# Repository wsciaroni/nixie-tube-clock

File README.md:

# nixie-tube-clock
Work in progress for designing and building a custom Nixie Tube Clock

## Starting Point

This project is incomplete.

I have started from the really helpful blog here: https://crystal.uta.edu/~burns/project_nixieclock.html

## Overview

I remember my first exposure to Nixie Tubes vividly. It was an old coin counting machine we were using for a change colection fund raiser. I was fascinated by the Nixie Tubes and have never forgotten them.

After observing many other Nixie Clock builds, I decided there wasn't one that met all of my needs.

The closest that I found was here: https://crystal.uta.edu/~burns/project_nixieclock.html. However, I would like a more accurate time. So, I plan to start with this project and modify it.  My goal is to

- Remove the LEDs (I don't really want a backlight)
- Change the embedded system to an ESP8266 / NodeMCU with WiFi to maintain time with the network
- Make sure the programming port is accessible so that I can reprogram or update the firmwware as needed

My Requirements for the clock are as follows

1. The clock needs to use Nixie Tubes
2. The Clock would sync with WiFi to keep a very accurate time
3. The high voltage supply's circuitry will be it's own board for modularity
4. It will be a 6 digit 24-hour clock (H1 H0 : M1 M0 : S1 S0)
5. The clock should be powered via 120V AC

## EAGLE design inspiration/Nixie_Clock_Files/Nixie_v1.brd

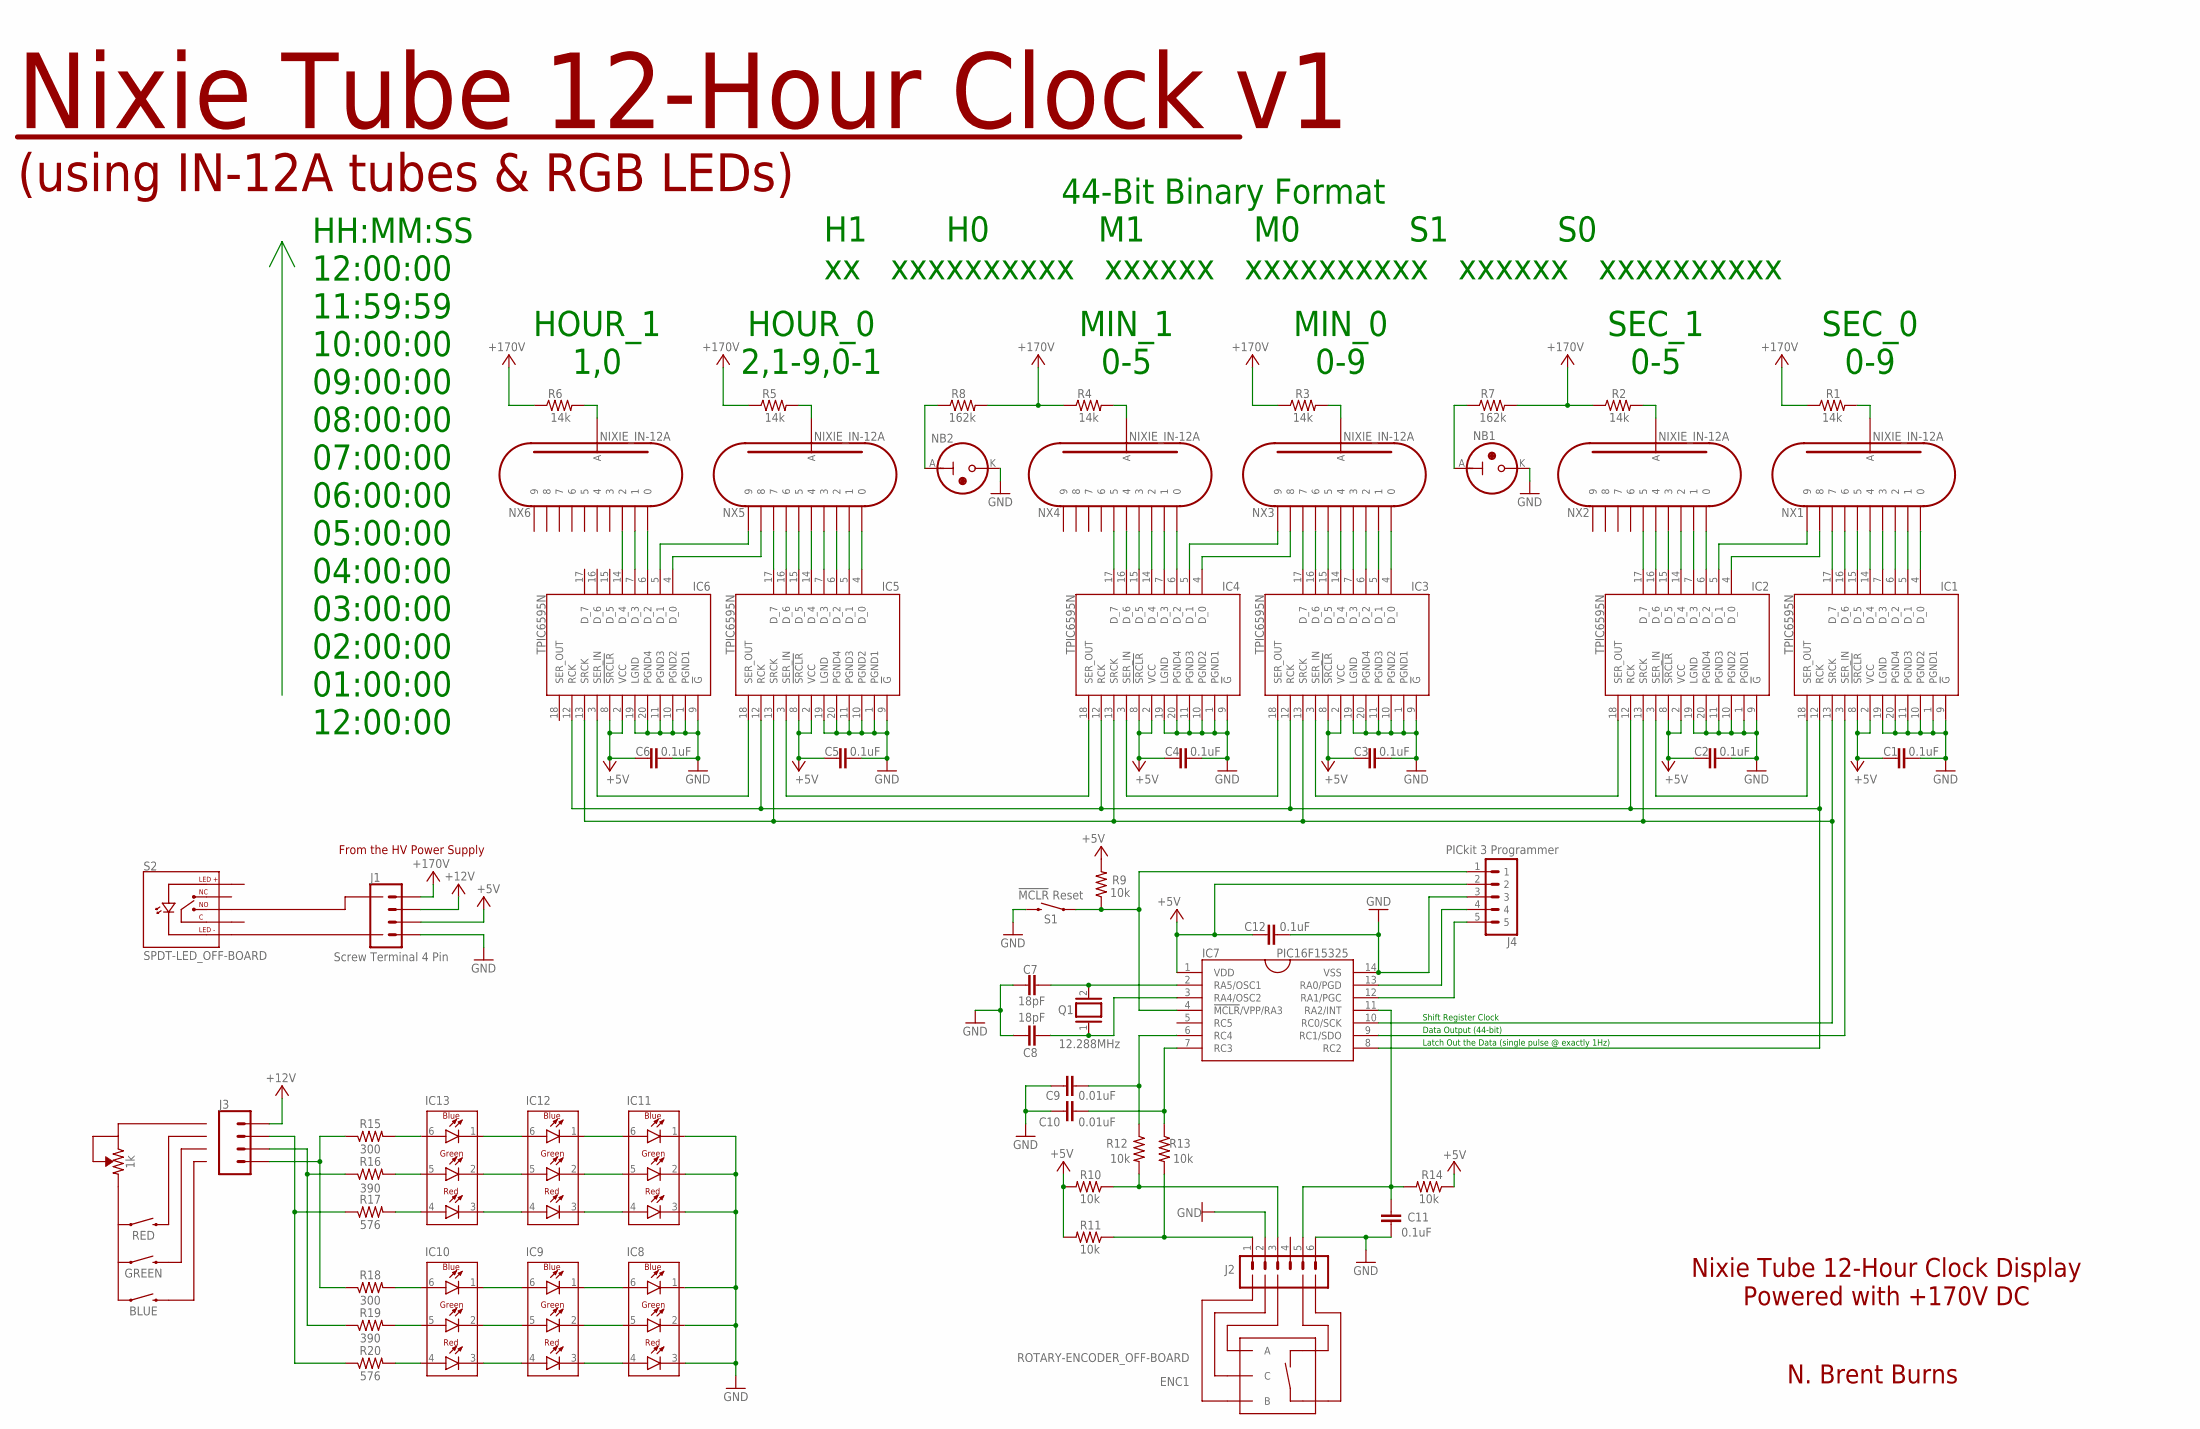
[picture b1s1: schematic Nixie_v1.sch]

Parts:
C1, C2, C3, C4, C5, C6, C11, C12: 0.1uF; C2.5-2
C7, C8: 18pF; C2.5-2
C9, C10: 0.01uF; C2.5-2
IC1, IC2, IC3, IC4, IC5, IC6: TPIC6595N; DIP20
IC7: PIC16F15325; DIP14
IC8, IC9, IC10, IC11, IC12, IC13: LED-RGB_CLY6D-FKC-CK1N1D1BB7D3D3; PLCC6-LED-RGB
J1: Screw Terminal 4 Pin; SCREW_TERM_5MM_1X4
J2: CONNECTOR_6PINSCREW_TERMINAL_5MM_PITCH; SCREW_TERM_5MM_1X6
J3: RGB Switches and 5k POT Connections; SCREW_TERM_5MM_1X4
J4: PICkit 3 Programmer; HEADER_2.54MM_1X5
NB1, NB2: IN-3
NX1, NX2, NX3, NX4, NX5, NX6: NIXIE_IN-12A; IN-12_NO_HOLE
Q1: 12.288MHz; QS
R1, R2, R3, R4, R5, R6: 14k; 0411/12
R7, R8: 162k; 0411/12
R9, R10, R11, R12, R13, R14: 10k; 0207/7
R15, R18: 300; 0207/7
R16, R19: 390; 0207/7
R17, R20: 576; 0207/7
S1: !MCLR! Reset; TACTILE_SWITCH_PTH_6.0MM
SYM101: SYMBOL_HIGH_VOLTAGE

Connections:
+5V: C1.2, C2.2, C3.2, C4.2, C5.2, C6.2, C12.1, IC1.2 (VCC), IC1.8 (!SRCLR), IC2.2 (VCC), IC2.8 (!SRCLR), IC3.2 (VCC), IC3.8 (!SRCLR), IC4.2 (VCC), IC4.8 (!SRCLR), IC5.2 (VCC), IC5.8 (!SRCLR), IC6.2 (VCC), IC6.8 (!SRCLR), IC7.1 (VDD), J1.2, J4.2, R9.2, R10.2, R11.2, R14.1
+12V: J1.3, J3.4
+170V: J1.4, R1.1, R2.1, R3.1, R4.1, R5.1, R6.1, R7.2, R8.2
GND: C1.1, C2.1, C3.1, C4.1, C5.1, C6.1, C7.2, C8.2, C9.2, C10.2, C11.1, C12.2, IC1.1 (PGND1), IC1.9 (!G), IC1.10 (PGND2), IC1.11 (PGND3), IC1.19 (LGND), IC1.20 (PGND4), IC2.1 (PGND1), IC2.9 (!G), IC2.10 (PGND2), IC2.11 (PGND3), IC2.19 (LGND), IC2.20 (PGND4), IC3.1 (PGND1), IC3.9 (!G), IC3.10 (PGND2), IC3.11 (PGND3), IC3.19 (LGND), IC3.20 (PGND4), IC4.1 (PGND1), IC4.9 (!G), IC4.10 (PGND2), IC4.11 (PGND3), IC4.19 (LGND), IC4.20 (PGND4), IC5.1 (PGND1), IC5.9 (!G), IC5.10 (PGND2), IC5.11 (PGND3), IC5.19 (LGND), IC5.20 (PGND4), IC6.1 (PGND1), IC6.9 (!G), IC6.10 (PGND2), IC6.11 (PGND3), IC6.19 (LGND), IC6.20 (PGND4), IC7.14 (VSS), IC8.1 (BLUE_CATHODE), IC8.2 (GREEN_CATHODE), IC8.3 (RED_CATHODE), IC11.1 (BLUE_CATHODE), IC11.2 (GREEN_CATHODE), IC11.3 (RED_CATHODE), J1.1, J2.2, J2.6, J4.3, NB1.K, NB2.K, S1.3 (2)
unnamed: IC1.4 (D_0), NX1.0
unnamed: IC1.5 (D_1), NX1.1
unnamed: IC1.6 (D_2), NX1.2
unnamed: IC1.7 (D_3), NX1.3
unnamed: IC1.14 (D_4), NX1.4
unnamed: IC1.15 (D_5), NX1.5
unnamed: IC1.16 (D_6), NX1.6
unnamed: IC1.17 (D_7), NX1.7
unnamed: NX1.A, R1.2
unnamed: NB2.A, R8.1
unnamed: NX2.A, R2.2
unnamed: NB1.A, R7.1
unnamed: NX3.A, R3.2
unnamed: NX4.A, R4.2
unnamed: NX5.A, R5.2
unnamed: NX6.A, R6.2
unnamed: IC5.4 (D_0), NX5.0
unnamed: IC5.5 (D_1), NX5.1
unnamed: IC2.4 (D_0), NX1.8
unnamed: IC2.5 (D_1), NX1.9
unnamed: IC7.12 (RA1/PGC), J4.5
unnamed: IC2.6 (D_2), NX2.0
unnamed: IC2.7 (D_3), NX2.1
unnamed: IC2.15 (D_5), NX2.3
unnamed: IC2.16 (D_6), NX2.4
unnamed: IC2.17 (D_7), NX2.5
unnamed: IC3.4 (D_0), NX3.0
unnamed: IC3.5 (D_1), NX3.1
unnamed: IC3.6 (D_2), NX3.2
unnamed: IC3.7 (D_3), NX3.3
unnamed: IC3.14 (D_4), NX3.4
unnamed: IC3.15 (D_5), NX3.5
unnamed: IC3.16 (D_6), NX3.6
unnamed: IC3.17 (D_7), NX3.7
unnamed: IC4.4 (D_0), NX3.8
unnamed: IC4.5 (D_1), NX3.9
unnamed: C7.1, IC7.2 (RA5/OSC1), Q1.2
unnamed: C8.1, IC7.3 (RA4/OSC2), Q1.1
unnamed: IC7.13 (RA0/PGD), J4.4
unnamed: IC4.15 (D_5), NX4.3
unnamed: IC4.16 (D_6), NX4.4
unnamed: IC4.17 (D_7), NX4.5
unnamed: IC5.6 (D_2), NX5.2
unnamed: IC5.7 (D_3), NX5.3
unnamed: IC5.14 (D_4), NX5.4
unnamed: IC5.15 (D_5), NX5.5
unnamed: IC5.16 (D_6), NX5.6
unnamed: IC5.17 (D_7), NX5.7
unnamed: IC6.4 (D_0), NX5.8
unnamed: IC6.5 (D_1), NX5.9
unnamed: IC6.6 (D_2), NX6.0
unnamed: IC6.7 (D_3), NX6.1
unnamed: IC5.18 (SER_OUT), IC6.3 (SER_IN)
unnamed: IC4.18 (SER_OUT), IC5.3 (SER_IN)
unnamed: IC3.18 (SER_OUT), IC4.3 (SER_IN)
unnamed: IC2.18 (SER_OUT), IC3.3 (SER_IN)
unnamed: IC1.18 (SER_OUT), IC2.3 (SER_IN)
unnamed: IC1.12 (RCK), IC2.12 (RCK), IC3.12 (RCK), IC4.12 (RCK), IC5.12 (RCK), IC6.12 (RCK), IC7.8 (RC2)
unnamed: IC2.14 (D_4), NX2.2
unnamed: IC1.13 (SRCK), IC2.13 (SRCK), IC3.13 (SRCK), IC4.13 (SRCK), IC5.13 (SRCK), IC6.13 (SRCK), IC7.10 (RC0/SCK)
unnamed: IC1.3 (SER_IN), IC7.9 (RC1/SDO)
unnamed: IC4.14 (D_4), NX4.2
unnamed: IC4.7 (D_3), NX4.1
unnamed: IC4.6 (D_2), NX4.0
unnamed: IC7.4 (!MCLR!/VPP/RA3), J4.1, R9.1, S1.1
unnamed: IC6.14 (D_4), NX6.2
unnamed: C11.2, IC7.11 (RA2/INT), J2.5, R14.2
unnamed: C10.1, IC7.7 (RC3), R13.1
unnamed: IC12.6 (BLUE_ANODE), IC13.1 (BLUE_CATHODE)
unnamed: IC11.6 (BLUE_ANODE), IC12.1 (BLUE_CATHODE)
unnamed: IC8.6 (BLUE_ANODE), IC9.1 (BLUE_CATHODE)
unnamed: IC9.6 (BLUE_ANODE), IC10.1 (BLUE_CATHODE)
unnamed: IC12.5 (GREEN_ANODE), IC13.2 (GREEN_CATHODE)
unnamed: IC11.5 (GREEN_ANODE), IC12.2 (GREEN_CATHODE)
unnamed: IC11.4 (RED_ANODE), IC12.3 (RED_CATHODE)
unnamed: IC12.4 (RED_ANODE), IC13.3 (RED_CATHODE)
unnamed: IC9.5 (GREEN_ANODE), IC10.2 (GREEN_CATHODE)
unnamed: IC8.5 (GREEN_ANODE), IC9.2 (GREEN_CATHODE)
unnamed: IC8.4 (RED_ANODE), IC9.3 (RED_CATHODE)
unnamed: IC9.4 (RED_ANODE), IC10.3 (RED_CATHODE)
unnamed: J2.3, R10.1, R12.2
unnamed: J2.1, R11.1, R13.2
unnamed: C9.1, IC7.6 (RC4), R12.1
unnamed: J3.1, R15.1, R18.1
unnamed: J3.2, R16.1, R19.1
unnamed: J3.3, R17.1, R20.1
unnamed: IC13.6 (BLUE_ANODE), R15.2
unnamed: IC13.5 (GREEN_ANODE), R16.2
unnamed: IC13.4 (RED_ANODE), R17.2
unnamed: IC10.6 (BLUE_ANODE), R18.2
unnamed: IC10.5 (GREEN_ANODE), R19.2
unnamed: IC10.4 (RED_ANODE), R20.2

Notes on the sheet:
SEC_0 0-9
SEC_1 0-5
MIN_0 0-9
MIN_1 0-5
HOUR_0 2,1-9,0-1
HOUR_1 1,0
Nixie Tube 12-Hour Clock v1
HH:MM:SS 12:00:00 11:59:59 10:00:00 09:00:00 08:00:00 07:00:00 06:00:00 05:00:00 04:00:00 03:00:00 02:00:00 01:00:00 12:00:00
(using IN-12A tubes & RGB LEDs)
Nixie Tube 12-Hour Clock Display Powered with +170V DC
N. Brent Burns
From the HV Power Supply
44-Bit Binary Format H1 H0 M1 M0 S1 S0 xx xxxxxxxxxx xxxxxx xxxxxxxxxx xxxxxx xxxxxxxxxx
Shift Register Clock
Data Output (44-bit)
Latch Out the Data (single pulse @ exactly 1Hz)

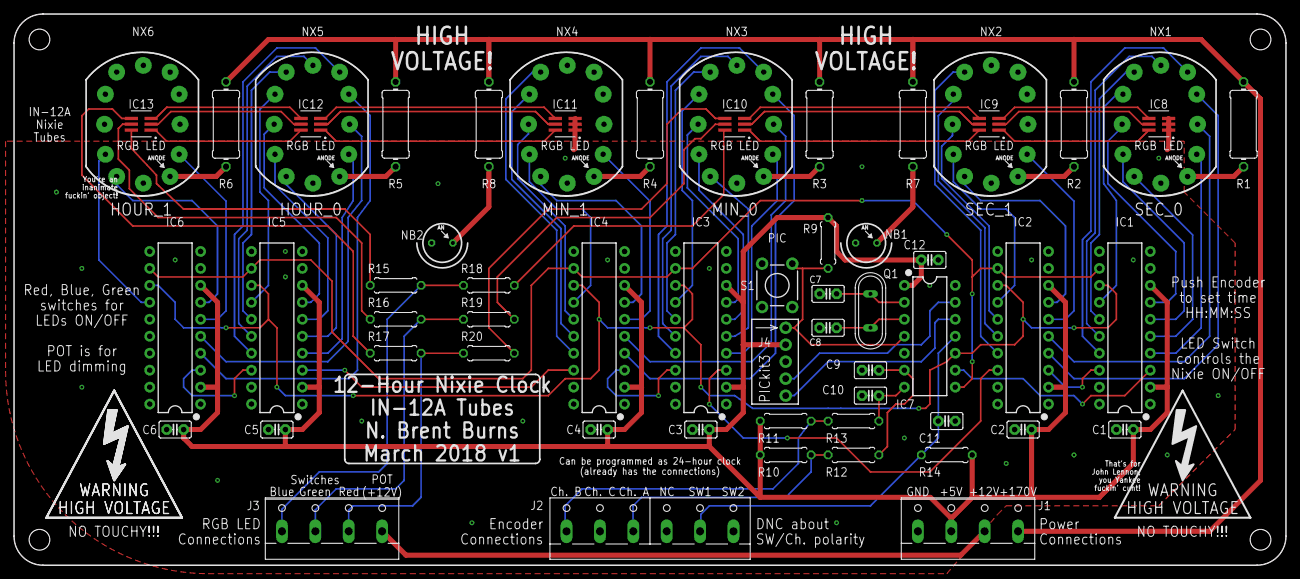
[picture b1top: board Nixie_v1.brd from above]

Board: 2 copper layers, 190.5 x 82.5 mm, 62 parts (0 on the bottom side), 96 nets.

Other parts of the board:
U$3, U$6: SYMBOL_HIGH_VOLTAGE

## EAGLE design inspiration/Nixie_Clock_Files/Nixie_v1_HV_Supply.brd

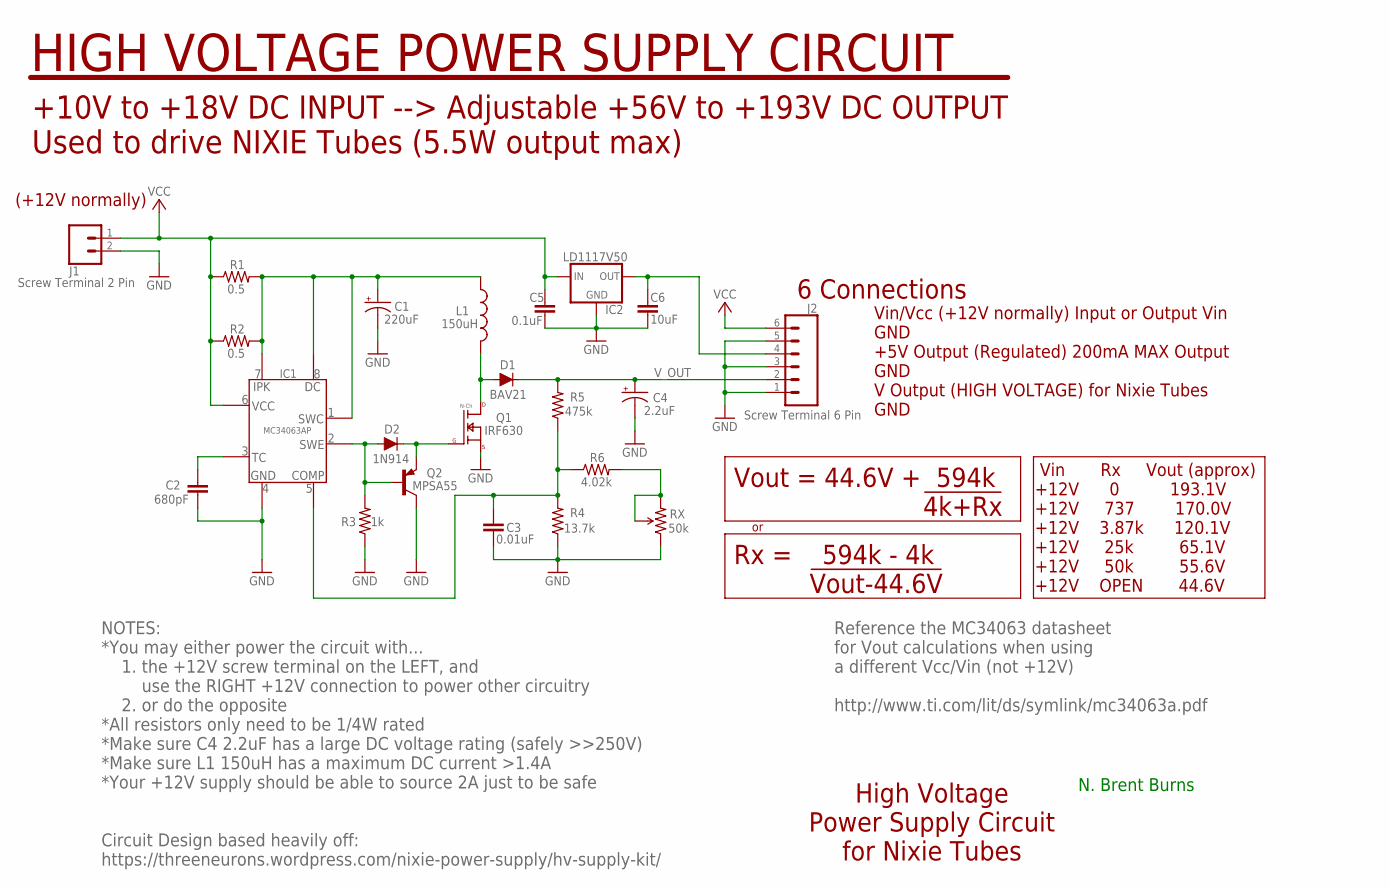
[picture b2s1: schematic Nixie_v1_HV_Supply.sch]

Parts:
C1: 220uF; CPOL-RADIAL-5MM-10MM
C2: 680pF; C2.5-2
C3: 0.01uF; C2.5-2
C4: 2.2uF; CPOL-RADIAL-2.5MM-6.5MM
C5: 0.1uF; C2.5-2
C6: 10uF; C2.5-2
D1: BAV21; DIODE-1N4148
D2: 1N914; DIODE-1N4148
IC1: MC34063AP; DIP08
IC2: LD1117V50; TO220V
J1: Screw Terminal 2 Pin; SCREW_TERM_5MM_1X2
J2: Screw Terminal 6 Pin; SCREW_TERM_5MM_1X6
L1: 150uH; INDUCTOR_11MM_DIAM_6MM_PITCH
Q1: IRF630; TO220V
Q2: MPSA55; TO92-
R1, R2: 0.5; 0204/7
R3: 1k; 0204/7
R4: 13.7k; 0204/7
R5: 475k; 0204/7
R6: 4.02k; 0204/7
RX: 50k; TRIM_POT_PTH

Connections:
GND: C1.-, C2.2, C3.2, C4.2 (-), C5.2, C6.2, IC1.4 (GND), IC2.1 (GND), J1.2, J2.1, J2.3, J2.5, Q1.3 (SOURCE), Q2.3 (C), R3.1, R4.1, RX.1 (CCW)
unnamed: C6.1, IC2.2 (OUT), J2.4
unnamed: D1.A, L1.2, Q1.2 (DRAIN)
unnamed: C4.1 (+), D1.C, J2.2, R5.2
unnamed: C2.1, IC1.3 (TC)
unnamed: C3.1, IC1.5 (COMP), R4.2, R5.1, R6.1
unnamed: C1.+, IC1.1 (SWC), IC1.7 (IPK), IC1.8 (DC), L1.1, R1.2, R2.2
unnamed: R6.2, RX.2 (WIPER), RX.3 (CW)
unnamed: D2.A, IC1.2 (SWE), Q2.2 (B), R3.2
unnamed: D2.C, Q1.1 (GATE), Q2.1 (E)
VCC: C5.1, IC1.6 (VCC), IC2.3 (IN), J1.1, J2.6, R1.1, R2.1

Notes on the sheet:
High Voltage Power Supply Circuit for Nixie Tubes
N. Brent Burns
HIGH VOLTAGE POWER SUPPLY CIRCUIT
+10V to +18V DC INPUT --> Adjustable +56V to +193V DC OUTPUT Used to drive NIXIE Tubes (5.5W output max)
V_OUT
Vin/Vcc (+12V normally) Input or Output Vin GND +5V Output (Regulated) 200mA MAX Output GND V Output (HIGH VOLTAGE) for Nixie Tubes GND
6 Connections
NOTES: *You may either power the circuit with... 1. the +12V screw terminal on the LEFT, and use the RIGHT +12V connection to power other circuitry 2. or do the opposite *All resistors only need to be 1/4W rated *Make sure C4 2.2uF has a large DC voltage rating (safely >>250V) *Make sure L1 150uH h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
Vout = 44.6V + 594k !4k+Rx!
Vin Rx Vout (approx) +12V 0 193.1V +12V 737 170.0V +12V 3.87k 120.1V +12V 25k 65.1V +12V 50k 55.6V +12V OPEN 44.6V
Rx = 594k - 4k !Vout-44.6V!
Circuit Design based heavily off: https://threeneurons.wordpress.com/nixie-power-supply/hv-supply-kit/
(+12V normally)
Reference the MC34063 datasheet for Vout calculations when using a different Vcc/Vin (not +12V) http://www.ti.com/lit/ds/symlink/mc34063a.pdf

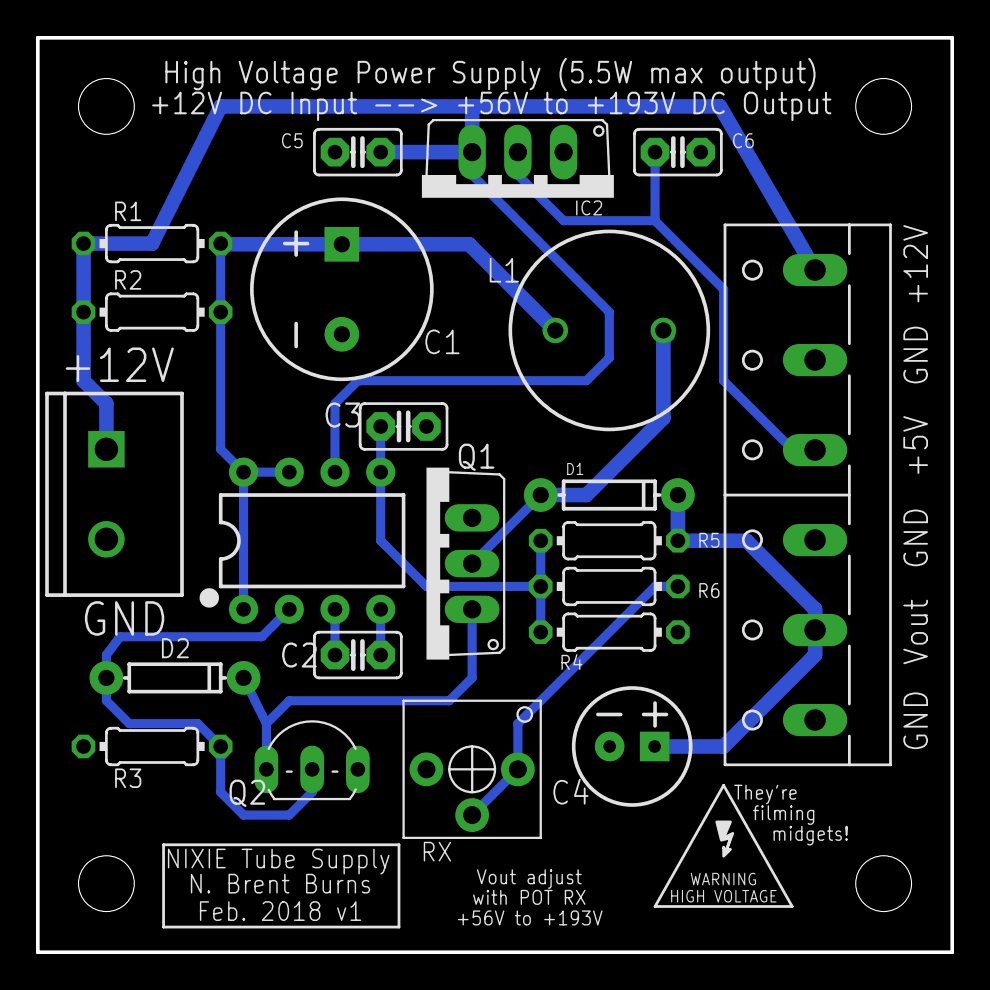
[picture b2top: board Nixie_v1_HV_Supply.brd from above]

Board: 1 copper layer, 50.8 x 50.8 mm, 22 parts (0 on the bottom side), 11 nets.

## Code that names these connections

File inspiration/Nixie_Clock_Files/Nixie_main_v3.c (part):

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 *                                     this RCK needs to happen every 1sec (EXACTLY)
 * 
 * PIC16F15325 Pins         Rotary Encoder Connections
 *  INT/RA2 (pin 11)---------------Push Button  (Normally pulled HIGH via resistor, pulsed LOW when user pressed the encoder's push button)
 *                                              (used as an External Interrupt to toggle through User Set Mode to adjust the clock's time)
 *  RC4 (pin 6)--------------------Channel A    (Ch. A and B used together to get direction (inc/dec) and adjust time when the user rotates the encoder)
 *  RC3 (pin 7)--------------------Channel B    (User must have previously pressed the Push Button for the rotation to adjust the time)
 *                                     
 * 
 * General structure (Free Running Mode):
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
#define _XTAL_FREQ 12288000 // Fosc = 12.288MHz (external crystal)

#define RCK_Latch_Signal    PORTCbits.RC2 // output IO pulse to latch out Shift Register data
#define Encoder_Ch_A        PORTCbits.RC4 // input from Channel A of the Encoder (RPG)
#define Encoder_Ch_B        PORTCbits.RC3 // input from Channel B of the Encoder (RPG)

#define MODE_FREE_RUNNING   0   // clock increments freely and normally
#define MODE_EDIT_HOURS     1   // user can use the encoder to select/adjust HOURS digits
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    
    // Turn off everything in the beginning
    RCK_Latch_Signal = 0;
    PORTCbits.RC0 = 0; // SCK/SCL
    PORTCbits.RC1 = 0; // SDO
    
    // PPS Settings (Peripheral Pin Select) (mapping)
    // want SDO on Pin 9 (RC1) & SCK on Pin 10 (RC0)
    RC0PPS = 0x15;   // RC0->MSSP1:SCK1;
    RC1PPS = 0x16;   // RC1->MSSP1:SDO1;
    
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
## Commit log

2023-01-11 Update README.md
    Add starting info
2023-01-11 Add Starting Project files
2023-01-11 Import Boards into KiCad from EAGLE
2023-01-11 Remove unused symbols from Schematic

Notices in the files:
parts and their libraries:
SparkFun-Switches: Licensing: Creative Commons ShareAlike 4.0 International - https://creativecommons.org/licenses/by-sa/4.0
